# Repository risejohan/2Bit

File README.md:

# 2 Bit Electronic 

##### Welcome to our space 🌍
We are electronic engineers focused on carrying out electronic developments, where they can be applied in favor of technology, the designs, modules and schemes can be used freely to be incorporated in their automation developments applied to the Internet of Things where it is based on interconnection digital of any product or object with any other around using the internet.

We have different Modules that can be used in electronic designs, implementations, prototypes and validations such as regulated sources, rtc, sd, ethernet, lora, lorawan among others, these can be applied to devices such as [stm32](https://www.st.com/en/microcontrollers-microprocessors/stm32-32-bit-arm-cortex-mcus.html "stm32"), [Arduino Uno](https://arduino.cl/arduino-uno/ "Arduino Uno"), [Mega](https://store.arduino.cc/products/arduino-mega-2560-rev3 "Mega"), [Esp32](https://www.espressif.com/en/products/socs/esp32 "Esp32") , [Esp8266](https://www.espressif.com/en/products/socs/esp8266 "Esp8266").

####Version 📌

For all available versions, look at the [tags in this repository](https://github.com/risejohan/2Bit/tree/main/module%20RTC/ds3231).

#### Authors ✒️
* **Johan Riascos** - *Electronic developer* - 
* [Github](https://github.com/risejohan)
* [Instagram Personal](https://instagram.com/johansegura92?utm_medium=copy_link)
* [Instagram 2bit](https://instagram.com/2bit_electronic?utm_medium=copy_link)

You can also look at the list of all the [contributors] (https://github.com/risejohan/2bit/contributors) who have participated in this project.

###  Expressions of gratitude 🎁
---
For the entire community that wishes to add and shows appreciation for sharing knowledge. Welcome to everyone who wishes to contribute in favor of technology.

#### Contributions
If you want to invite us to a coffee ☕ and contribute to continue uploading  content ⬆ . You can do it here 👇🏻
⌨️ con ❤️❤️❤️ [Donation](https://paypal.me/2bitelectronic "Donation") 😊

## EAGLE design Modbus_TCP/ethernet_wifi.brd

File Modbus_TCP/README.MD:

# Module Ethernet - Wifi - Modbus

## Start 🚀

_Be able to use the designs of the common modules to have available and apply to electronic designs._

### Pre requirements 📋

_Connectivity module that has functions using the ethernet-wifi-modbus 485 protocol._

### Conditions and Characteristic🔩
Its main Controller for the ethernet has the internal stack to carry out the communication tcp / ip w5100, it has a tool that opens an endless number of ways to control your Arduino through the Internet or your home LAN. Home automation, automation, Internet of things (IoT), remote control and monitoring, etc., are some of the fields where this shield can be used. It is compatible with Arduino Uno, Mega and Leonardo. In addition, the Ethernet and SD libraries are included by default, the microcontroller in charge of making it is a WROM esp32, it has external storage using SD
###### Technical specifications
Input voltage: 4.5-5V
Output current: Maximum 300mA
Ethernet chip: Wiznet W5100
Ethernet speed: 10/100 Mbps
RJ45 connector
Interface: SPI
Compatible with Arduino Uno, Mega, Leonardo
MicroSD Card reader

MAC address: 0xDE, 0xAD, 0xBE, 0xEF, 0xFE, 0xED
byte mac[] = { 0xDE, 0xAD, 0xBE, 0xEF, 0xFE, 0xED }

## Built with 🛠️

Development sofware:
[Eagle](https://www.autodesk.com/products/eagle/overview) - Electronic design software

### Components
- ESP32
- MAX485    
- Wiznet W5100
- SD

## Version 📌

For all available versions, look at the [tags in this repository](https://github.com/risejohan/2Bit/tree/main/module%20RTC/ds3231).

## Authors ✒️
* **Johan Riascos** - *Electronic developer* - 
* [Github](https://github.com/risejohan)
* [Instagram Personal](https://instagram.com/johansegura92?utm_medium=copy_link)
* [Instagram 2bit](https://instagram.com/2bit_electronic?utm_medium=copy_link)

You can also look at the list of all the [contributors] (https://github.com/risejohan/2bit/contributors) who have participated in this project.

###  Expressions of gratitude 🎁
---
For the entire community that wishes to add and shows appreciation for sharing knowledge. Welcome to everyone who wishes to contribute in favor of technology.

#### Contributions
If you want to invite us to a coffee ☕ and contribute to continue uploading  content ⬆ . You can do it here 👇🏻
⌨️ con ❤️❤️❤️ [Donation](https://paypal.me/2bitelectronic "Donation") 😊

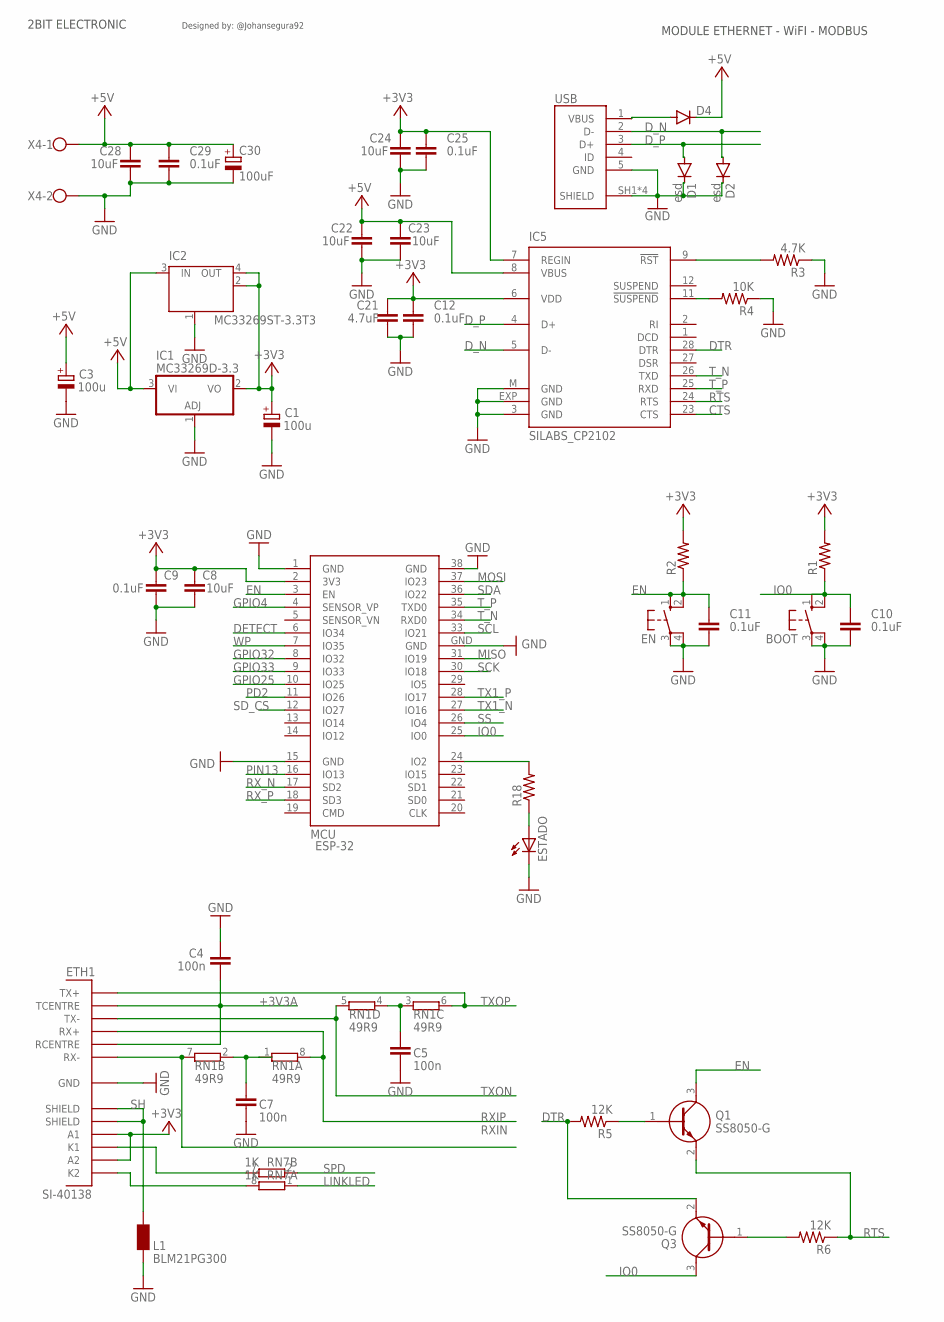
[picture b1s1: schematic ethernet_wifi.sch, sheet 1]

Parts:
BOOT: 10-XX; B3F-10XX
C1, C3: 100u; PANASONIC_D
C4, C5, C7: 100n; C0603
C8, C22, C23, C24, C28: 10uF; C0805K
C9, C10, C11, C12, C25, C29: 0.1uF; C0805K
C21: 4.7uF; C0805K
C30: 100uF; E2-5
D1, D2: esd; SOD123
D4: DIODE-SOD123; SOD123
EN: 10-XX; B3F-10XX
ESTADO: LEDCHIP-LED0805; CHIP-LED0805
ETH1: SI-40138; SI40138
IC1: MC33269D-3.3; DPACK
IC2: MC33269ST-3.3T3; SOT223
IC5: SILABS_CP2102; SILABS_MLP28
L1: BLM21PG300; 0805
MCU: ESP-32
Q1, Q3: SS8050-G; SOT95P240X115-3N
R1, R2, R18: R-US_R0805; R0805
R3: 4.7K; R0805
R4: 10K; R0805
R5, R6: 12K; R0805
RN1: 49R9; CAY16
RN7: 1K; CAY16
USB: MICRO-USB_2040002-1; MICRO-USB_TE_2040002-1
X4: W237-102

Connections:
+3V3: C1.+, C8.1, C9.1, C12.1, C21.1, C24.1, C25.1, ETH1.9 (A1), ETH1.11 (A2), IC1.2 (VO), IC2.2 (OUT), IC2.4 (OUT), IC5.6 (VDD), IC5.7 (REGIN), MCU.2 (3V3), R1.2, R2.2; also elsewhere on the board
+3V3A: C4.1, ETH1.2 (TCENTRE), ETH1.5 (RCENTRE); also elsewhere on the board
+5V: C3.+, C22.1, C23.1, C28.1, C29.1, C30.+, D4.C, IC1.3 (VI), IC2.3 (IN), IC5.8 (VBUS), X4.1; also elsewhere on the board
CTS: IC5.23 (CTS)
DETECT: MCU.6 (IO34); also elsewhere on the board
DTR: IC5.28 (DTR), Q3.2 (E), R5.2
D_N: D2.A, IC5.5 (D-), USB.2 (D-)
D_P: D1.A, IC5.4 (D+), USB.3 (D+)
EN: C11.1, EN.1 (S), EN.2 (S1), MCU.3 (EN), Q1.3 (C), R2.1
GND: BOOT.3, BOOT.4 (P1), C1.-, C3.-, C4.2, C5.1, C7.1, C8.2, C9.2, C10.2, C11.2, C12.2, C21.2, C22.2, C23.2, C24.2, C25.2, C28.2, C29.2, C30.-, D1.C, D2.C, EN.3, EN.4 (P1), ESTADO.C, ETH1.8 (GND), IC1.1 (ADJ), IC2.1 (GND/ADJ), IC5.3 (GND), IC5.EXP (GND), IC5.M (GND), L1.1, MCU.1 (GND), MCU.15 (GND), MCU.38 (GND), MCU.GND, R3.1, R4.1, USB.5 (GND), USB.SH1 (SHIELD), USB.SH2 (SHIELD), USB.SH3 (SHIELD), USB.SH4 (SHIELD), X4.2; also elsewhere on the board
GPIO4: MCU.4 (SENSOR_VP); also elsewhere on the board
GPIO25: MCU.10 (IO25); also elsewhere on the board
GPIO32: MCU.8 (IO32); also elsewhere on the board
GPIO33: MCU.9 (IO33); also elsewhere on the board
IO0: BOOT.1 (S), BOOT.2 (S1), C10.1, MCU.25 (IO0), Q3.3 (C), R1.1
LINKLED: RN7.1; also elsewhere on the board
MISO: MCU.31 (IO19); also elsewhere on the board
MOSI: MCU.37 (IO23); also elsewhere on the board
unnamed: C5.2, RN1.3 (1), RN1.4 (1)
unnamed: IC5.9 (!RST), R3.2
unnamed: D4.A, USB.1 (VBUS)
unnamed: IC5.11 (!SUSPEND), R4.2
unnamed: ETH1.10 (K1), RN7.7 (2)
unnamed: ETH1.12 (K2), RN7.8 (2)
unnamed: Q3.1 (B), R6.2
unnamed: Q1.1 (B), R5.1
unnamed: ESTADO.A, R18.1
unnamed: MCU.24 (IO2), R18.2
unnamed: C7.2, RN1.1, RN1.2 (1)
PD2: MCU.11 (IO26); also elsewhere on the board
PIN13: MCU.16 (IO13); also elsewhere on the board
RTS: IC5.24 (RTS), Q1.2 (E), R6.1
RXIN: ETH1.6 (RX-), RN1.7 (2); also elsewhere on the board
RXIP: ETH1.4 (RX+), RN1.8 (2); also elsewhere on the board
RX_N: MCU.17 (SD2); also elsewhere on the board
RX_P: MCU.18 (SD3); also elsewhere on the board
SCK: MCU.30 (IO18); also elsewhere on the board
SCL: MCU.33 (IO21); also elsewhere on the board
SDA: MCU.36 (IO22); also elsewhere on the board
SD_CS: MCU.12 (IO27); also elsewhere on the board
SH: ETH1.S1 (SHIELD), ETH1.S2 (SHIELD), L1.2
SPD: RN7.2 (1); also elsewhere on the board
SS: MCU.26 (IO4); also elsewhere on the board
TX1_N: MCU.27 (IO16); also elsewhere on the board
TX1_P: MCU.28 (IO17); also elsewhere on the board
TXON: ETH1.3 (TX-), RN1.5 (2); also elsewhere on the board
TXOP: ETH1.1 (TX+), RN1.6 (2); also elsewhere on the board
T_N: IC5.26 (TXD), MCU.34 (RXD0)
T_P: IC5.25 (RXD), MCU.35 (TXD0)
WP: MCU.7 (IO35); also elsewhere on the board

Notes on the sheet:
2BIT ELECTRONIC
MODULE ETHERNET - WiFI - MODBUS
Designed by: @Johansegura92

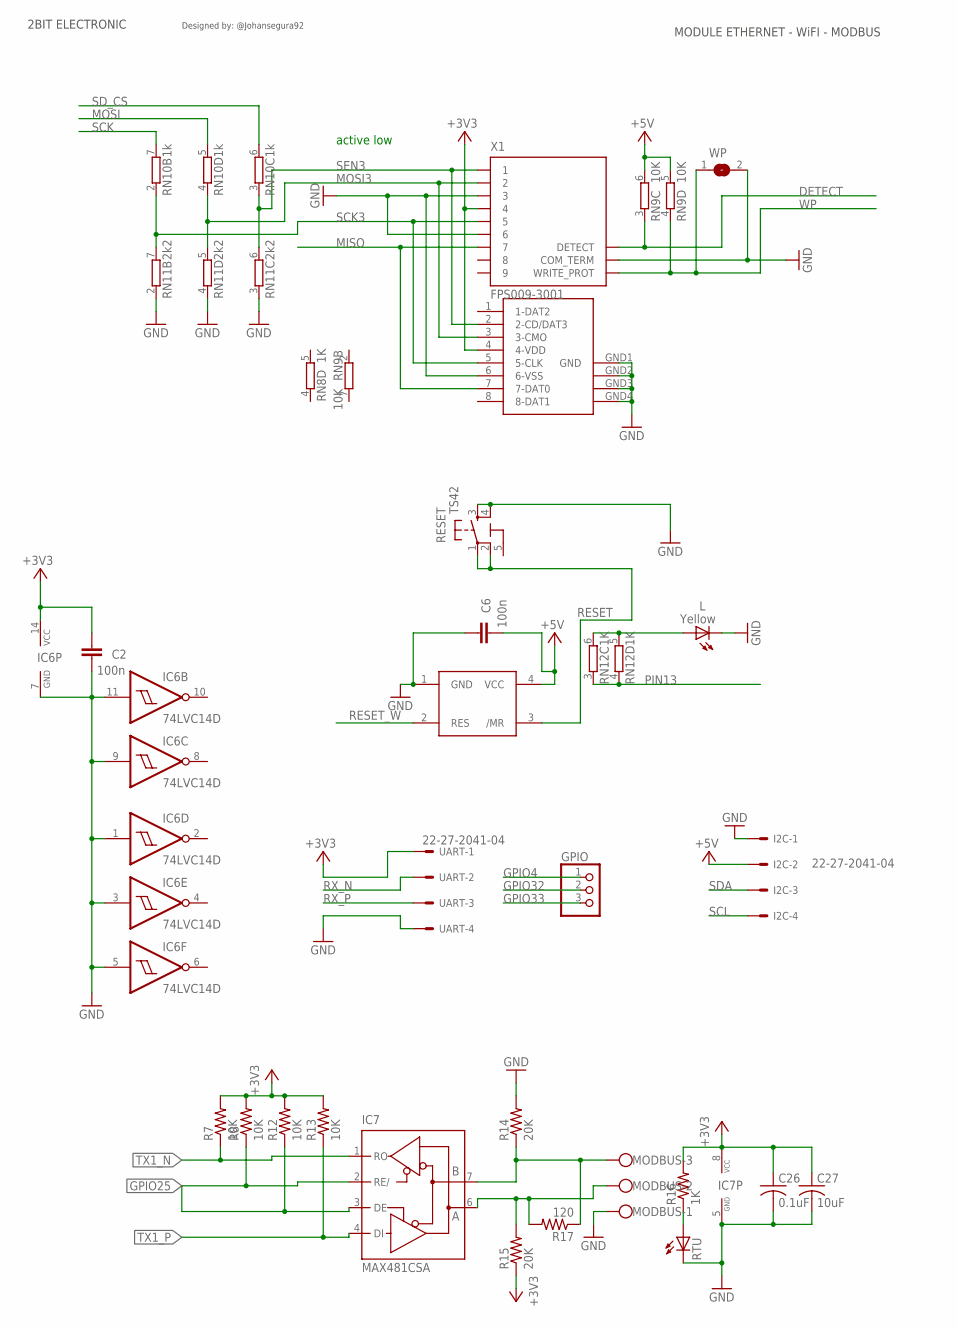
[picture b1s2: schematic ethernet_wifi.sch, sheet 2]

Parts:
C2, C6: 100n; C0603
C26: 0.1uF; C0805K
C27: 10uF; C0805K
GPIO: PINHD-1X3; 1X03
I2C: 22-27-2041-04; 6410-04
IC6: 74LVC14D; SO14
IC7: MAX481CSA; SO08
L: Yellow; CHIPLED_0805
MODBUS: W237-103
R7, R8, R12, R13: 10K; M0805
R14, R15: 20K; M0805
R16: 1K; M0805
R17: 120; M0805
RESET: TS42
RN8, RN12: 1K; CAY16
RN9: 10K; CAY16
RN10: 1k; CAY16
RN11: 2k2; CAY16
RTU: LEDCHIP-LED0805; CHIP-LED0805
U2: STM812; SOT143
UART: 22-27-2041-04; 6410-04
WP: SJ
X1: FPS009-3001; FPS009-3000
X2: SDCARD-15TW-8821

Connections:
5-GND: RESET.5 (5-GND)
+3V3: C2.2, C26.1, C27.1, IC6.14 (VCC), IC7.8 (VCC), R7.2, R8.2, R12.2, R13.2, R15.1, R16.2, UART.1, X1.4, X2.4 (4-VDD); also elsewhere on the board
+5V: C6.1, I2C.2, RN9.5 (2), RN9.6 (2), U2.4 (VCC); also elsewhere on the board
DETECT: RN9.3 (1), X1.DETECT; also elsewhere on the board
GND: C2.1, C6.2, C26.2, C27.2, I2C.1, IC6.1 (I), IC6.3 (I), IC6.5 (I), IC6.7 (GND), IC6.9 (I), IC6.11 (I), IC7.5 (GND), L.C, MODBUS.1, R14.2, RESET.3, RESET.4, RN11.2 (1), RN11.3 (1), RN11.4 (1), RTU.C, U2.1 (GND), UART.4, WP.2, X1.3, X1.6, X1.COM_TERM, X2.6 (6-VSS), X2.GND1 (GND), X2.GND2 (GND1), X2.GND3 (GND2), X2.GND4 (GND3); also elsewhere on the board
GPIO4: GPIO.1; also elsewhere on the board
GPIO25: IC7.2 (RE/), IC7.3 (DE), R8.1, R12.1; also elsewhere on the board
GPIO32: GPIO.2; also elsewhere on the board
GPIO33: GPIO.3; also elsewhere on the board
MISO: X1.7, X2.7 (7-DAT0); also elsewhere on the board
MOSI: RN10.5 (2); also elsewhere on the board
MOSI3: RN10.4 (1), RN11.5 (2), X1.2, X2.3 (3-CMO)
unnamed: L.A, RN12.5 (2), RN12.6 (2)
unnamed: IC7.7 (B), MODBUS.3, R14.1, R17.1
unnamed: IC7.6 (A), MODBUS.2, R15.2, R17.2
unnamed: R16.1, RTU.A
PIN13: RN12.3 (1), RN12.4 (1); also elsewhere on the board
RESET: RESET.1, RESET.2, U2.3 (/MR)
RESET_W: U2.2 (RES); also elsewhere on the board
RX_N: UART.2; also elsewhere on the board
RX_P: UART.3; also elsewhere on the board
SCK: RN10.7 (2); also elsewhere on the board
SCK3: RN10.2 (1), RN11.7 (2), X1.5, X2.5 (5-CLK)
SCL: I2C.4; also elsewhere on the board
SDA: I2C.3; also elsewhere on the board
SD_CS: RN10.6 (2); also elsewhere on the board
SEN3: RN10.3 (1), RN11.6 (2), X1.1, X2.2 (2-CD/DAT3)
TX1_N: IC7.1 (RO), R7.1; also elsewhere on the board
TX1_P: IC7.4 (DI), R13.1; also elsewhere on the board
WP: RN9.4 (1), WP.1, X1.WRITE_PROT; also elsewhere on the board

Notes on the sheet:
active low
2BIT ELECTRONIC
MODULE ETHERNET - WiFI - MODBUS
Designed by: @Johansegura92

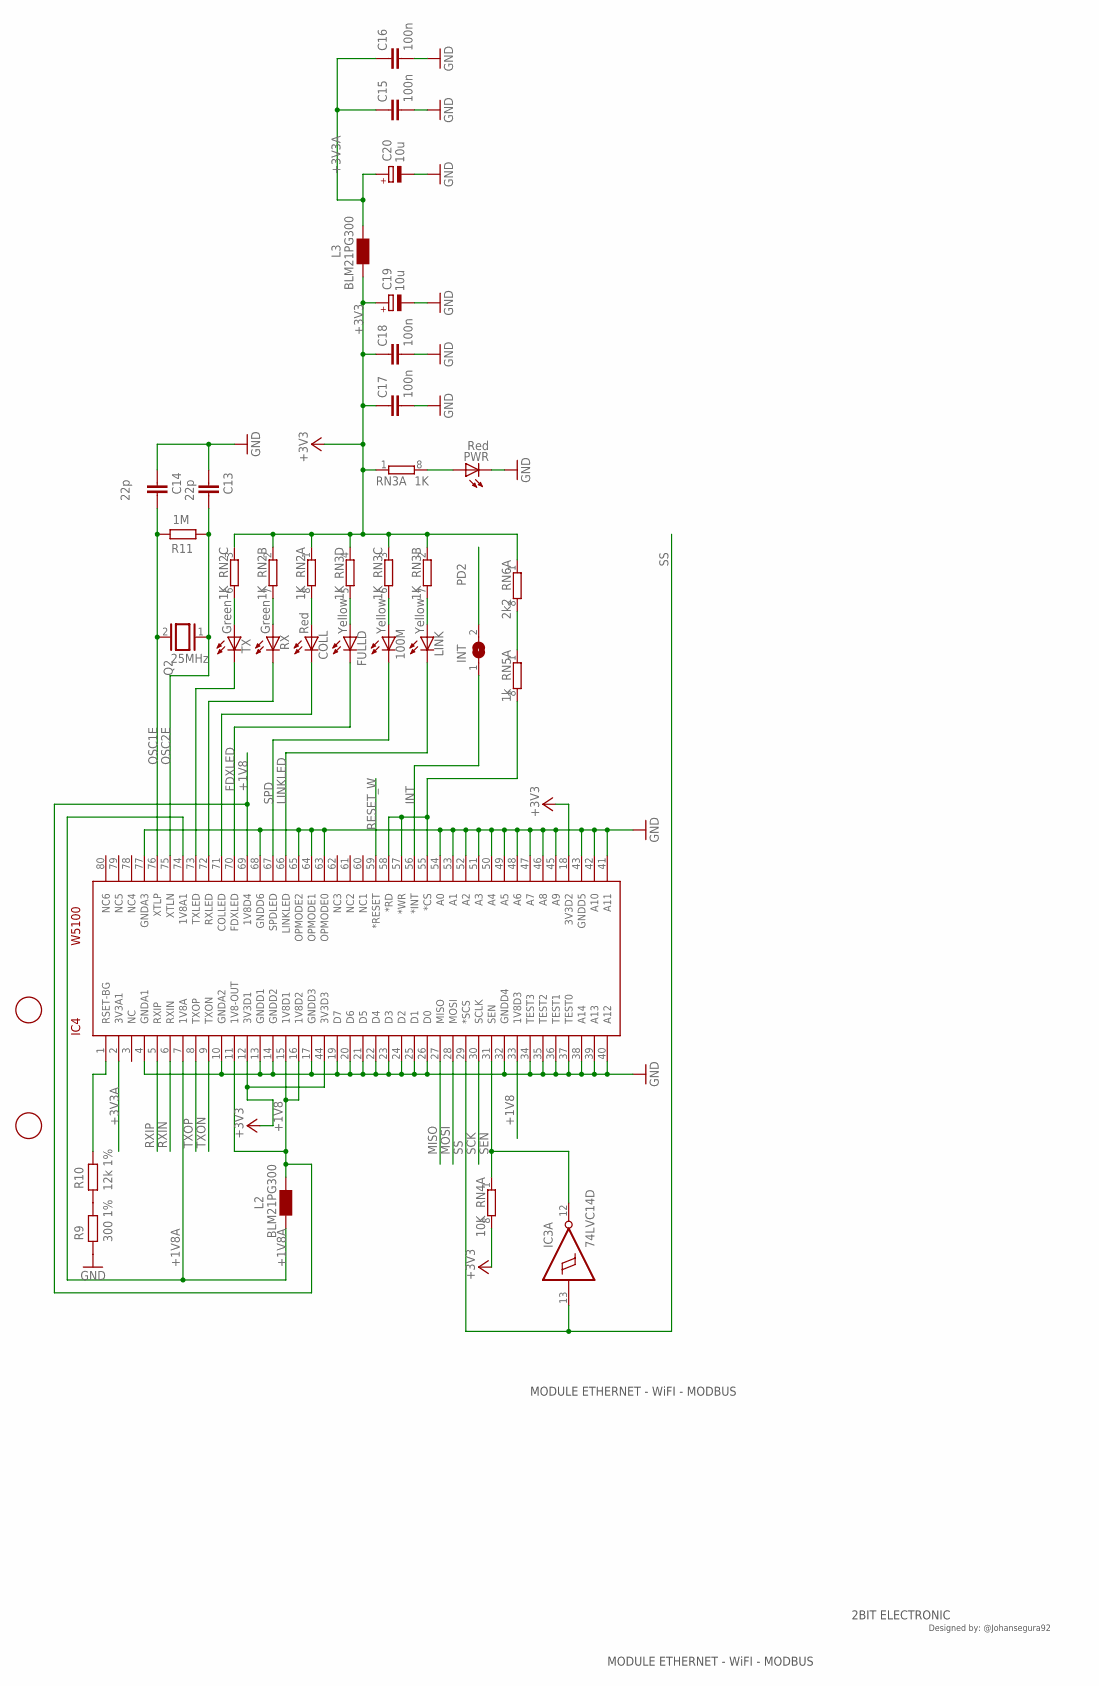
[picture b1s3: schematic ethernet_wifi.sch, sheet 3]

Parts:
100M: Yellow; CHIPLED_0805
C13, C14: 22p; C0603
C15, C16, C17, C18: 100n; C0603
C19, C20: 10u; SMC_B
COLL: Red; CHIPLED_0805
F1, F4: FIDUCIALMOUNT; FIDUCIA-MOUNT
FULLD: Yellow; CHIPLED_0805
IC3: 74LVC14D; SO14
IC4: W5100; SQFP-S-10X10-80
INT: SJ
L2, L3: BLM21PG300; 0805
LINK: Yellow; CHIPLED_0805
PWR: Red; CHIPLED_0805
Q2: 25MHz; QS
R9: 300 1%; R0603
R10: 12k 1%; R0603
R11: 1M; R0603
RN2, RN3: 1K; CAY16
RN4: 10K; CAY16
RN5: 1k; CAY16
RN6: 2k2; CAY16
RX: Green; CHIPLED_0805
TX: Green; CHIPLED_0805

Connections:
+1V8: IC4.11 (1V8-OUT), IC4.15 (1V8D1), IC4.16 (1V8D2), IC4.33 (1V8D3), IC4.69 (1V8D4), L2.1
+1V8A: IC4.7 (1V8A), IC4.74 (1V8A1), L2.2
+3V3: C17.1, C18.1, C19.+, IC4.12 (3V3D1), IC4.18 (3V3D2), IC4.44 (3V3D3), L3.2, RN2.1, RN2.2 (1), RN2.3 (1), RN3.1, RN3.2 (1), RN3.3 (1), RN3.4 (1), RN4.8 (2), RN6.1; also elsewhere on the board
+3V3A: C15.1, C16.1, C20.+, IC4.2 (3V3A1), L3.1; also elsewhere on the board
FDXLED: FULLD.C, IC4.70 (FDXLED)
GND: C13.1, C14.1, C15.2, C16.2, C17.2, C18.2, C19.-, C20.-, IC3.7 (GND), IC4.4 (GNDA1), IC4.10 (GNDA2), IC4.13 (GNDD1), IC4.14 (GNDD2), IC4.17 (GNDD3), IC4.19 (D7), IC4.20 (D6), IC4.21 (D5), IC4.22 (D4), IC4.23 (D3), IC4.24 (D2), IC4.25 (D1), IC4.26 (D0), IC4.32 (GNDD4), IC4.34 (TEST3), IC4.35 (TEST2), IC4.36 (TEST1), IC4.37 (TEST0), IC4.38 (A14), IC4.39 (A13), IC4.40 (A12), IC4.41 (A11), IC4.42 (A10), IC4.43 (GNDD5), IC4.45 (A9), IC4.46 (A8), IC4.47 (A7), IC4.48 (A6), IC4.49 (A5), IC4.50 (A4), IC4.51 (A3), IC4.52 (A2), IC4.53 (A1), IC4.54 (A0), IC4.63 (OPMODE0), IC4.64 (OPMODE1), IC4.65 (OPMODE2), IC4.68 (GNDD6), IC4.77 (GNDA3), PWR.C, R9.2; also elsewhere on the board
INT: IC4.56 (*INT), INT.1
LINKLED: IC4.66 (LINKLED), LINK.C; also elsewhere on the board
MISO: IC4.27 (MISO); also elsewhere on the board
MOSI: IC4.28 (MOSI); also elsewhere on the board
unnamed: PWR.A, RN3.8 (2)
unnamed: IC4.55 (*CS), IC4.57 (*WR), IC4.58 (*RD), RN5.8 (2)
unnamed: IC4.73 (TXLED), TX.C
unnamed: IC4.72 (RXLED), RX.C
unnamed: COLL.C, IC4.71 (COLLED)
unnamed: RN2.6 (2), TX.A
unnamed: RN5.1, RN6.8 (2)
unnamed: RN2.7 (2), RX.A
unnamed: COLL.A, RN2.8 (2)
unnamed: FULLD.A, RN3.5 (2)
unnamed: 100M.A, RN3.6 (2)
unnamed: LINK.A, RN3.7 (2)
unnamed: R9.1, R10.2
unnamed: IC4.1 (RSET-BG), R10.1
OSC1E: C14.2, IC4.76 (XTLP), Q2.2, R11.2
OSC2E: C13.2, IC4.75 (XTLN), Q2.1, R11.1
PD2: INT.2; also elsewhere on the board
RESET_W: IC4.59 (*RESET); also elsewhere on the board
RXIN: IC4.6 (RXIN); also elsewhere on the board
RXIP: IC4.5 (RXIP); also elsewhere on the board
SCK: IC4.30 (SCLK); also elsewhere on the board
SEN: IC3.12 (O), IC4.31 (SEN), RN4.1
SPD: 100M.C, IC4.67 (SPDLED); also elsewhere on the board
SS: IC3.13 (I), IC4.29 (*SCS); also elsewhere on the board
TXON: IC4.9 (TXON); also elsewhere on the board
TXOP: IC4.8 (TXOP); also elsewhere on the board
VCC: IC3.14 (VCC)

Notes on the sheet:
2BIT ELECTRONIC
MODULE ETHERNET - WiFI - MODBUS
Designed by: @Johansegura92

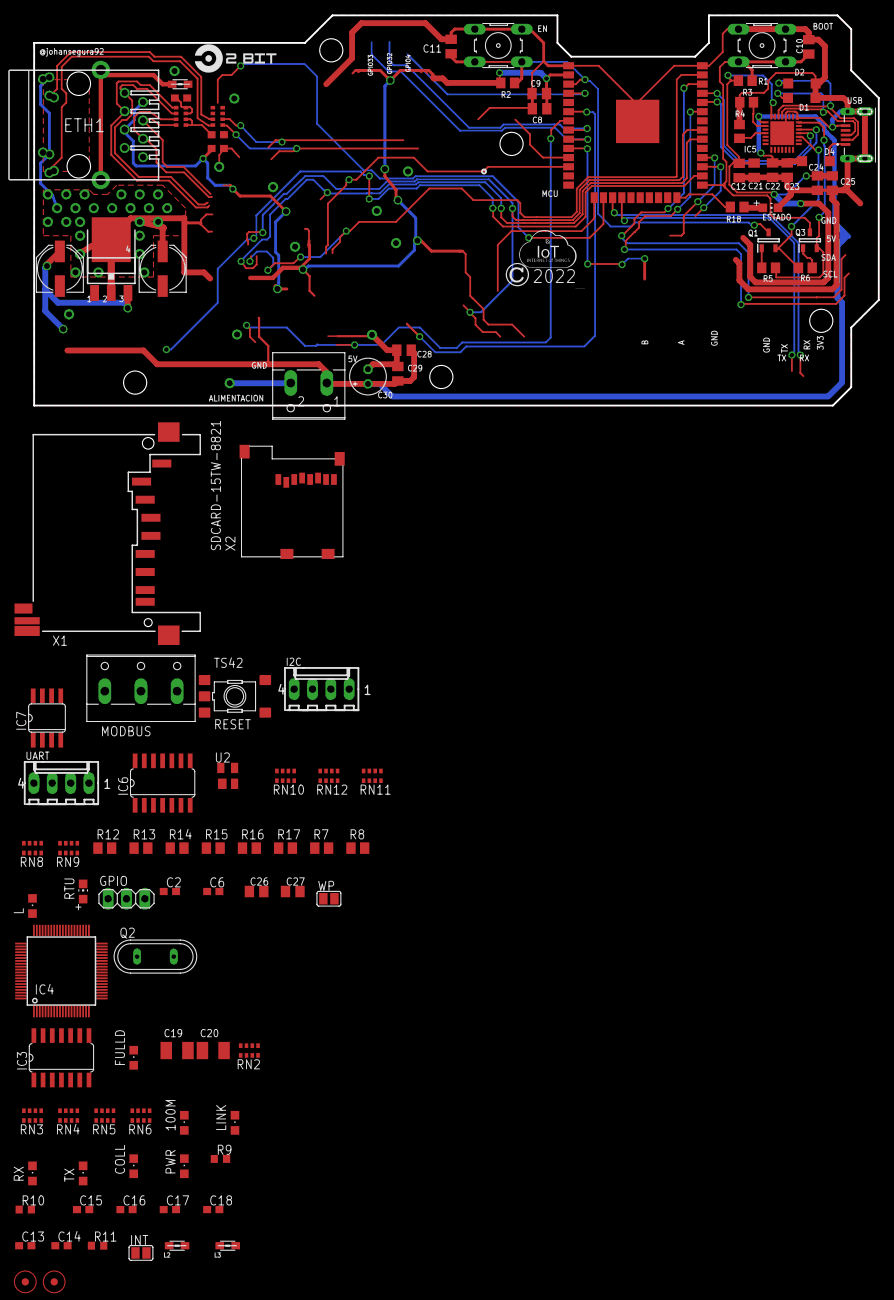
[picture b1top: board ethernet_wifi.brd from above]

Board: 2 copper layers, 116.8 x 54.0 mm, 104 parts (0 on the bottom side), 79 nets.

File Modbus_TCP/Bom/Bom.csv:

Qty;Value;Device;Package;Parts;Description;;;;;;;;;;;;;;
2;;10-XX;B3F-10XX;BOOT, EN;OMRON SWITCH;;;;;;;;;;;;;;
1;;DIODE-SOD123;SOD123;D4;DIODE;;;;;;;;;;;;;;
2;;LEDCHIP-LED0805;CHIP-LED0805;ESTADO, RTU;LED;;;;;;;;;;;;;;
1;;PINHD-1X3;1X03;GPIO;PIN HEADER;;;;;;;;;;;;;;
3;;R-US_R0805;R0805;R1, R2, R18;RESISTOR, American symbol;;;;;;;;;;;;;;
2;;SJ;SJ;INT, WP;SMD solder JUMPER;;;;;;;;;;;;;;
1;;W237-102;W237-102;X4;WAGO SCREW CLAMP;;;;;;;;;;;;;;
1;;W237-103;W237-103;MODBUS;WAGO SCREW CLAMP;;;;;;;;;;;;;;
6;0.1uF;C-EUC0805K;C0805K;C9, C10, C11, C12, C25, C29;CAPACITOR, European symbol;;;;;;;;;;;;;;
1;0.1uF;C-USC0805K;C0805K;C26;CAPACITOR, American symbol;;;;;;;;;;;;;;
9;100n;C-EUC0603;C0603;C2, C4, C5, C6, C7, C15, C16, C17, C18;CAPACITOR, European symbol;;;;;;;;;;;;;;
2;100u;CPOL-EUD;PANASONIC_D;C1, C3;POLARIZED CAPACITOR, European symbol;;;;;;;;;;;;;;
1;100uF;CPOL-EUE2-5;E2-5;C30;POLARIZED CAPACITOR, European symbol;;;;;;;;;;;;;;
2;10K;4R-NCAY16;CAY16;RN4, RN9;Array Chip Resistor;;;;;;;;;;;;;;
4;10K;R-US_M0805;M0805;R7, R8, R12, R13;RESISTOR, American symbol;;;;;;;;;;;;;;
1;10K;R-US_R0805;R0805;R4;RESISTOR, American symbol;;;;;;;;;;;;;;
2;10u;CPOL-EUSMCB;SMC_B;C19, C20;POLARIZED CAPACITOR, European symbol;;;;;;;;;;;;;;
5;10uF;C-EUC0805K;C0805K;C8, C22, C23, C24, C28;CAPACITOR, European symbol;;;;;;;;;;;;;;
1;10uF;C-USC0805K;C0805K;C27;CAPACITOR, American symbol;;;;;;;;;;;;;;
1;120;R-US_M0805;M0805;R17;RESISTOR, American symbol;;;;;;;;;;;;;;
2;12K;R-US_R0805;R0805;R5, R6;RESISTOR, American symbol;;;;;;;;;;;;;;
1;12k 1%;R-EU_R0603;R0603;R10;RESISTOR, European symbol;;;;;;;;;;;;;;
5;1K;4R-NCAY16;CAY16;RN2, RN3, RN7, RN8, RN12;Array Chip Resistor;;;;;;;;;;;;;;
1;1K;R-US_M0805;M0805;R16;RESISTOR, American symbol;;;;;;;;;;;;;;
1;1M;R-EU_R0603;R0603;R11;RESISTOR, European symbol;;;;;;;;;;;;;;
2;1k;4R-NCAY16;CAY16;RN5, RN10;Array Chip Resistor;;;;;;;;;;;;;;
2;20K;R-US_M0805;M0805;R14, R15;RESISTOR, American symbol;;;;;;;;;;;;;;
2;22-27-2041-04;22-27-2041-04;6410-04;I2C, UART;CONNECTOR;;;;;;;;;;;;;;
2;22p;C-EUC0603;C0603;C13, C14;CAPACITOR, European symbol;;;;;;;;;;;;;;
1;25MHz;XTAL/S;QS;Q2;CRYSTAL;;;;;;;;;;;;;;
2;2k2;4R-NCAY16;CAY16;RN6, RN11;Array Chip Resistor;;;;;;;;;;;;;;
1;300 1%;R-EU_R0603;R0603;R9;RESISTOR, European symbol;;;;;;;;;;;;;;
1;4.7K;R-US_R0805;R0805;R3;RESISTOR, American symbol;;;;;;;;;;;;;;
1;4.7uF;C-EUC0805K;C0805K;C21;CAPACITOR, European symbol;;;;;;;;;;;;;;
1;49R9;4R-NCAY16;CAY16;RN1;Array Chip Resistor;;;;;;;;;;;;;;
2;74LVC14D;74LS14D;SO14;IC3, IC6;Hex schmitt trigger INVERTER;;;;;;;;;;;;;;
3;BLM21PG300;WE-CBF_0805;805;L1, L2, L3;SMD EMI Suppression Ferrite Beads;;;;;;;;;;;;;;
1;ESP-32;ESP-32;ESP-32;MCU;Espressif Systems ESP-WROOM-32;;;;;;;;;;;;;;
2;FIDUCIALMOUNT;FIDUCIALMOUNT;FIDUCIA-MOUNT;F1, F4;;;;;;;;;;;;;;;
1;FPS009-3001;FPS009-3001;FPS009-3000;X1;SD Card and MMC Reader (Manual Insertion);;;;;;;;;;;;;;
2;Green;LEDCHIPLED_0805;CHIPLED_0805;RX, TX;LED;;;;;;;;;;;;;;
1;MAX481CSA;MAX481CSA;SO08;IC7;RS485 TRANSEIVER;;;;;;;;;;;;;;
1;MC33269D-3.3;MC33269D-3.3;DPACK;IC1;Adjustable Output Low Dropout Voltage Regulator 800 mA;;;;;;;;;;;;;;
1;MC33269ST-3.3T3;MC33269ST-3.3T3;SOT223;IC2;Adjustable Output Low Dropout Voltage Regulator 800 mA;;;;;;;;;;;;;;
1;MICRO-USB_2040002-1;MICRO-USB_2040002-1;MICRO-USB_TE_2040002-1;USB;Conn USB Type B RCP 5 POS 0.65mm Solder RA SMD 5 Terminal 1 Port T/R;;;;;;;;;;;;;;
2;Red;LEDCHIPLED_0805;CHIPLED_0805;COLL, PWR;LED;;;;;;;;;;;;;;
1;SDCARD-15TW-8821;SDCARD-15TW-8821;SDCARD-15TW-8821;X2;SD Card;;;;;;;;;;;;;;
1;SI-40138;SI-40138;SI40138;ETH1;Ethernet Jack with Integrated Magnetics;;;;;;;;;;;;;;
1;SILABS_CP2102;SILABS_CP2102;SILABS_MLP28;IC5;Single-Chip USB to UART Bridge;;;;;;;;;;;;;;
2;SS8050-G;SS8050-G;SOT95P240X115-3N;Q1, Q3;Bipolar Transistors - BJT NPN TRANSISTOR 1.5A 40V;;;;;;;;;;;;;;
1;STM812;STM812;SOT143;U2;;;;;;;;;;;;;;;
1;TS42;TS42;TS42;RESET;TS42;;;;;;;;;;;;;;
1;W5100;W5100;SQFP-S-10X10-80;IC4;;;;;;;;;;;;;;;
4;Yellow;LEDCHIPLED_0805;CHIPLED_0805;100M, FULLD, L, LINK;LED;;;;;;;;;;;;;;
2;esd;DIODE-SOD123;SOD123;D1, D2;DIODE;;;;;;;;;;;;;;22

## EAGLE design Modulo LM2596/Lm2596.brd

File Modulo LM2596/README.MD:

# Dc-Dc Step down

## Start 🚀

_Be able to use the designs of the common modules to have available and apply to electronic designs._

### Pre requirements 📋

_The LM2596 series of regulators are monolithic integrated circuits that provide all the active functions for a step-down (buck) switching regulator, capable of driving a 3-A load with excellent line and load regulation. These devices are available in fixed output voltages of 3.3 V, 5 V, 12 V, and an adjustable output version_

### Conditions and Characteristic🔩

It is capable of conducting a current of up to 3A. It handles a load with excellent line regulation and low ripple voltage. This device is available with adjustable output voltage

###### Dc-Dc step down
Based on the LM2596 regulator, output between 1.5 and 35Vdc
Input voltage: 4.5-40V
Output voltage: 1.5-35V (Adjustable)
Output current: Maximum 3A
Switching frequency: 150 KHz

#### Links

- [Lm2596](https://www.ti.com/lit/ds/symlink/lm2596.pdf?ts=1638989805405&ref_url=https%253A%252F%252Fwww.ti.com%252Fproduct%252FLM2596)

## Built with 🛠️

Development sofware:
[Eagle](https://www.autodesk.com/products/eagle/overview) - Electronic design software

### Components
- Trimmer
- Leds
- Terminal Block
- Resistor
- Diode

## Version 📌

For all available versions, look at the [tags in this repository](https://github.com/risejohan/2Bit/tree/main/module%20RTC/ds3231).

## Authors ✒️
* **Johan Riascos** - *Electronic developer* - 
* [Github](https://github.com/risejohan)
* [Instagram Personal](https://instagram.com/johansegura92?utm_medium=copy_link)
* [Instagram 2bit](https://instagram.com/2bit_electronic?utm_medium=copy_link)

You can also look at the list of all the [contributors] (https://github.com/risejohan/2bit/contributors) who have participated in this project.

###  Expressions of gratitude 🎁
---
For the entire community that wishes to add and shows appreciation for sharing knowledge. Welcome to everyone who wishes to contribute in favor of technology.

#### Contributions
If you want to invite us to a coffee ☕ and contribute to continue uploading  content ⬆ . You can do it here 👇🏻
⌨️ con ❤️❤️❤️ [Donation](https://paypal.me/2bitelectronic "Donation") 😊

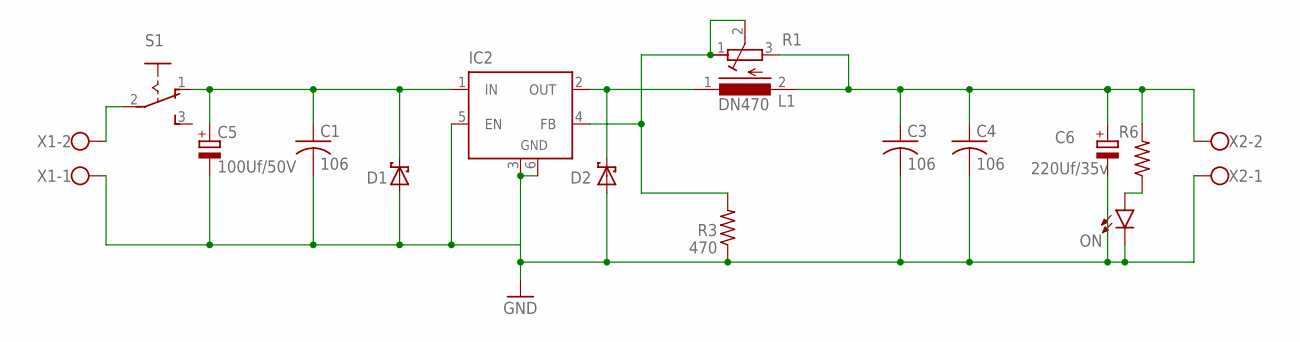
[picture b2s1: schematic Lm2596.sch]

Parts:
C1, C3, C4: 106; C0805K
C5: 100Uf/50V; 140CLH-0810
C6: 220Uf/35v; 140CLH-0810
D1, D2: SCHOTTKY-DIODE; DIODE_SMB
IC2: LM2596S; TO263-5
L1: DN470; DR127
ON: LEDCHIP-LED0805; CHIP-LED0805
R1: R-TRIMMT93YA; RTRIMT93YA
R3: 470; R0805
R6: 330; R0805
S1: M251
X1, X2: W237-102

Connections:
+5V1: C3.1, C4.1, C6.+, L1.2, R1.3 (A), R6.2, X2.2
GND: C1.2, C3.2, C4.2, C5.-, C6.-, D1.A (C), D2.A (C), IC2.3 (GND), IC2.5 (EN), IC2.6 (GND), ON.C, R3.1, X1.1, X2.1
IN1: C1.1, C5.+, D1.C (A), IC2.1 (IN), S1.1 (O)
unnamed: D2.C (A), IC2.2 (OUT), L1.1
unnamed: S1.2, X1.2
unnamed: IC2.4 (FB), R1.1 (E), R1.2 (S), R3.2
unnamed: ON.A, R6.1

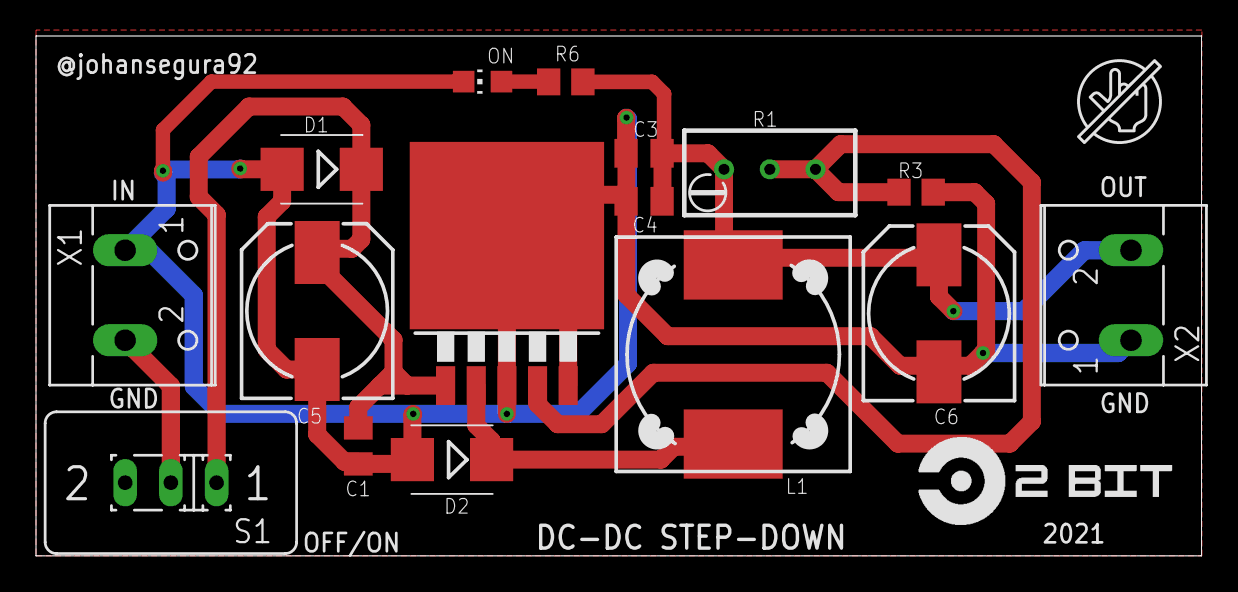
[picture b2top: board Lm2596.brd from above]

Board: 2 copper layers, 64.8 x 28.9 mm, 16 parts (0 on the bottom side), 7 nets.

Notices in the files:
parts and their libraries:
SparkFun-DiscreteSemi: Licensing: Creative Commons ShareAlike 4.0 International - https://creativecommons.org/licenses/by-sa/4.0
SparkFun-Passives: Licensing: CC v3.0 Share-Alike You are welcome to use this library for commercial purposes.
